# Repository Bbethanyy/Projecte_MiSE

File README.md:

View this project on [CADLAB.io](https://cadlab.io/project/27800). 

# Projecte_MiSE

**Membres del grup:** Bethany Quintero i Rossend Cera
----------------------------------------------------
## Objectiu
Dissenyar un sistema per controlar els moviments de'un Robot mitjançant un Microcontrolador MSP430.

## Elements
- Una placa base amb el Microcontrolador MSP430
- Connexió SBW o JTAG per poder programar/debugar amb una eina externa.
- Un DISPLAY LCD 
- Un Comandament format per un joystick i 1 o 2 polsadors
- El ROBOT 1(DFRobot Mcqueen plus)
- Dues LDRs
- Un mòdul UART<->Wifi

  ## Diagrama de blocs
)

## Components
| Ref. | Descripció| Datasheet |
| ------ | -----------------| ------------------|
|MSP430FR2355TPT|Microcontrolador|[Datasheet](https://www.ti.com/lit/ds/symlink/msp430fr2355.pdfts=1708776366062&ref_url=https%253A%252F%252Fwww.ti.com%252Fproduct%252FMSP430FR2355%253Fqgpn%253Dmsp430fr2355)|
|THB-1841844|Joystick| [Datasheet](https://www.mouser.es/datasheet/2/240/thb-3050713.pdf)|
|HD44780U|LCD 1602|[Datasheet](https://www.sparkfun.com/datasheets/LCD/HD44780.pdf)|
|MD21605B6W-FPTLWI3| LCD I2C| [Datasheet](https://www.farnell.com/datasheets/3164276.pdf)|
|MCCOG21605B6W-SPTLYI| LCD Text | [Datasheet](https://www.farnell.com/datasheets/2021773.pdf)|
|NSL-19M51|Detector de fotos| [Datasheet](file:///C:/Users/betha/AppData/Local/Temp/817923a0-e29a-454a-975b-60c01e8ddaef_Documents%20components%20i%20dispositius-20240224.zip.aef/LDR%20NSL-19M51.pdf)|
|...| LMV324| [Datasheet](https://www.ti.com/lit/ds/symlink/lmv324.pdf)|
|...| Trimmer tyco| [Datasheet](https://www.farnell.com/datasheets/314461.pdf)|
|...| Ultrasons HC-SR04| [Datasheet](file:///C:/Users/betha/AppData/Local/Temp/49233692-ea68-4fa0-998a-116c9ef42827_Documents%20components%20i%20dispositius-20240224.zip.827/Ultrasons%20HC-SR04%20Echo%20Locator%20Making%20it%20better.pdf)|
|...| Ultrasons HC-SR05| [Datasheet](file:///C:/Users/betha/AppData/Local/Temp/bb4ae17f-42be-418a-a625-329d45a58329_Documents%20components%20i%20dispositius-20240224.zip.329/Ultrasons%20HC-SR05_Ultrasonic_Module%20VMA306%20Schema.pdf)|
|...| Ultrasons SRF04| [Datasheet](file:///C:/Users/betha/AppData/Local/Temp/166e3fce-a4a8-462c-85ff-759b14133cc4_Documents%20components%20i%20dispositius-20240224.zip.cc4/Ultrasons%20SRF04%20Technical%20Documentation.pdf)|

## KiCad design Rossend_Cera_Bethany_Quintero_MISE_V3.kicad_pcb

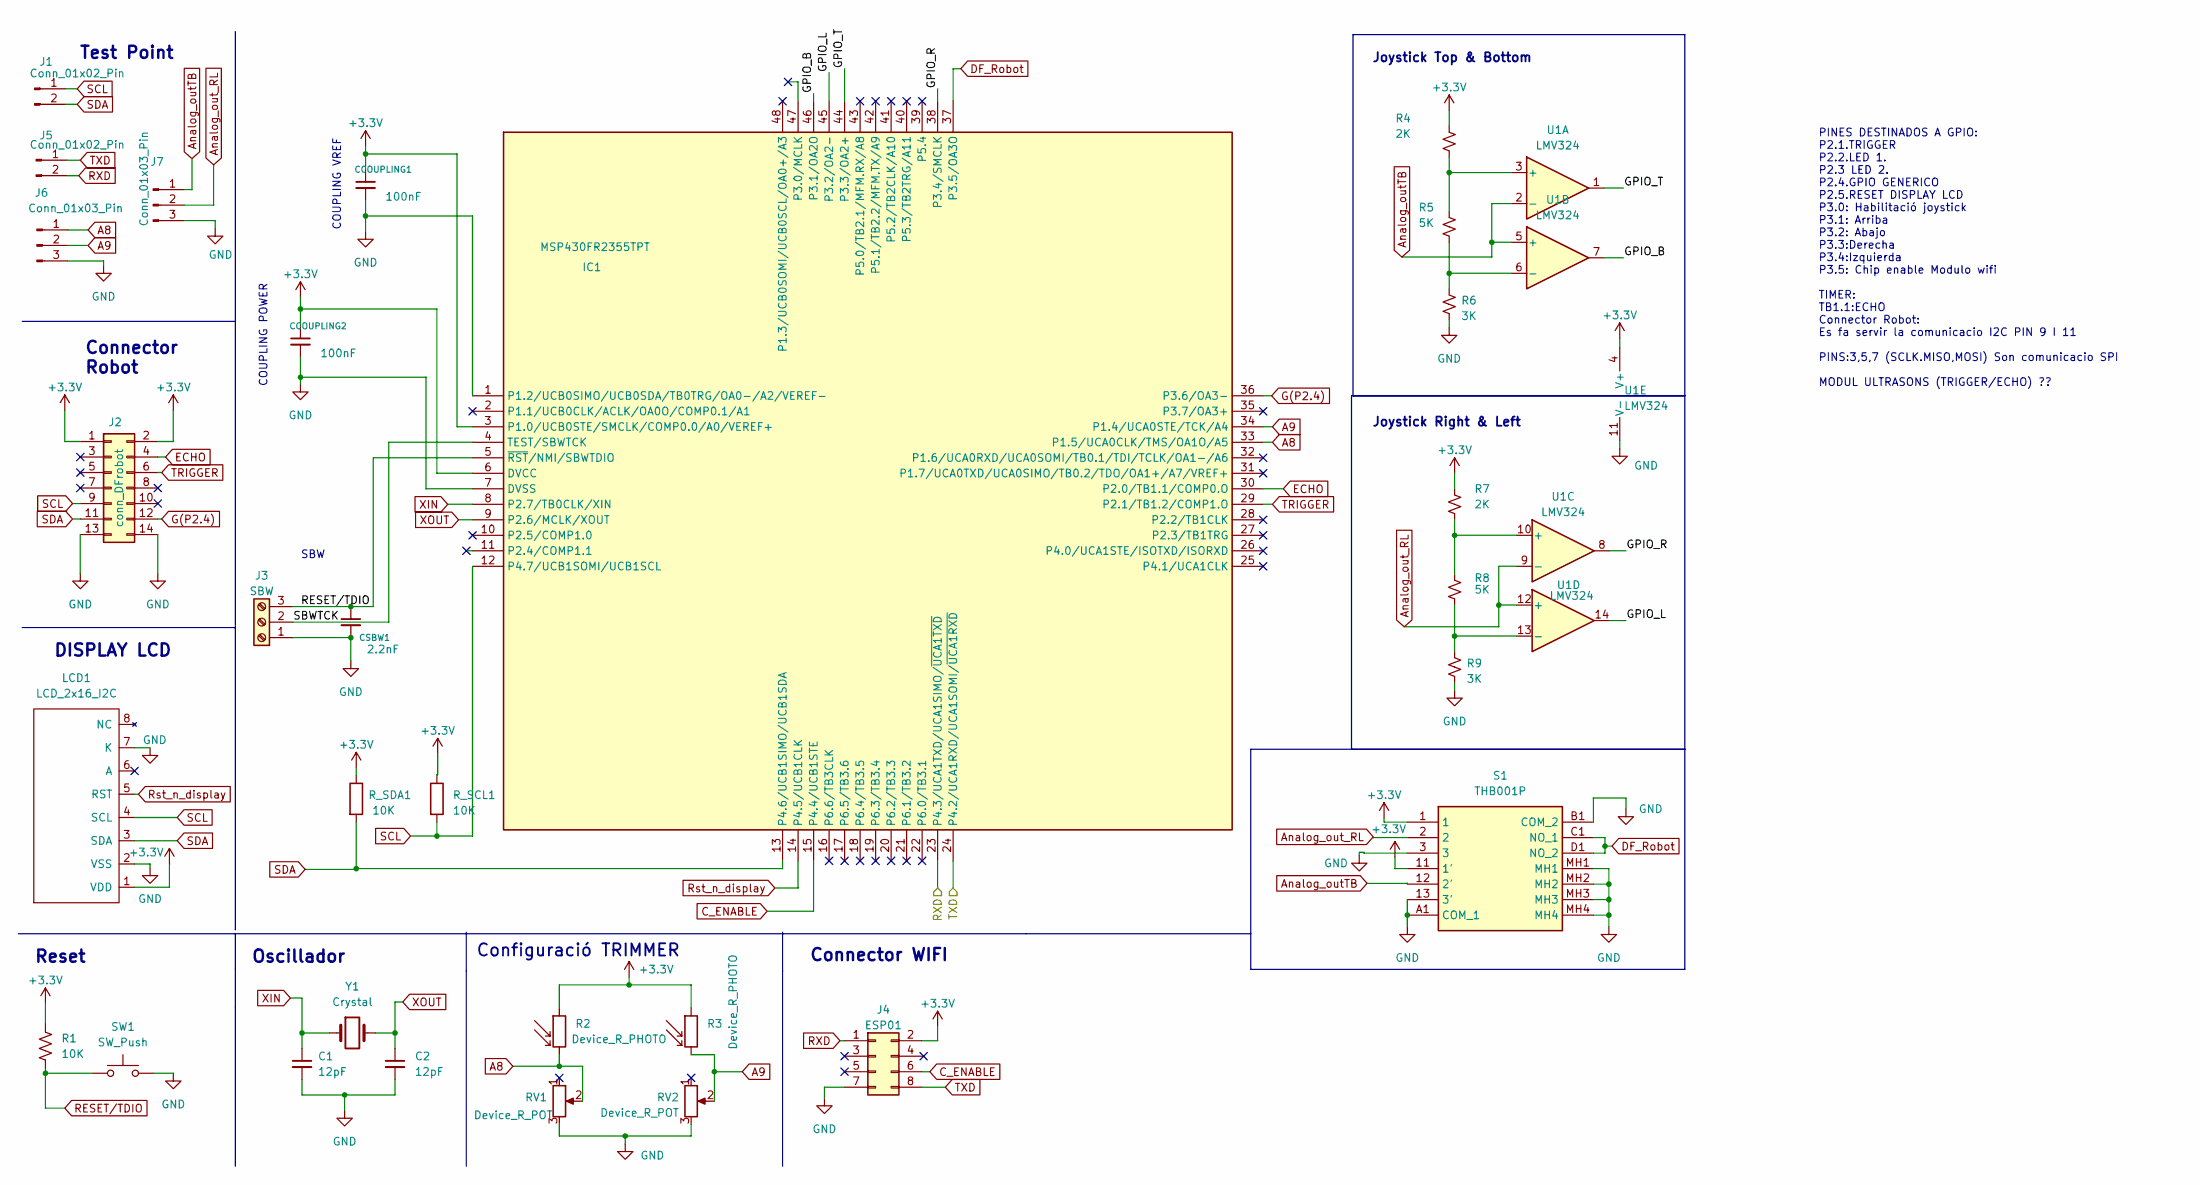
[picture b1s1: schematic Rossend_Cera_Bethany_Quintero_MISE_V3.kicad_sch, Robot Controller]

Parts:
C1, C2: 12pF; C_0805_2012Metric_Pad1.18x1.45mm_HandSolder
CCOUPLING1, CCOUPLING2: 100nF; C_0805_2012Metric_Pad1.18x1.45mm_HandSolder
CSBW1: 2.2nF; C_0805_2012Metric_Pad1.18x1.45mm_HandSolder
IC1: MSP430FR2355TPT; QFP50P900X900X160-48N; Manufacturer_Part_Number MSP430FR2355TPT; Mouser Part Number 595-MSP430FR2355TPT
J1, J5: Conn_01x02_Pin; PinHeader_1x02_P2.54mm_Vertical
J2: conn_DFrobot
J3: SBW; PinHeader_1x03_P2.54mm_Vertical
J4: ESP01; PinHeader_2x04_P2.54mm_Vertical
J6, J7: Conn_01x03_Pin; PinHeader_1x03_P2.54mm_Vertical
LCD1: LCD_2x16_I2C; LCD_2x16_I2C(Midas)
R1: 10K; R_0805_2012Metric_Pad1.20x1.40mm_HandSolder
R2, R3: Device_R_PHOTO; LDR
R4, R7: 2K; R_0805_2012Metric_Pad1.20x1.40mm_HandSolder
R5, R8: 5K; R_0805_2012Metric_Pad1.20x1.40mm_HandSolder
R6, R9: 3K; R_0805_2012Metric_Pad1.20x1.40mm_HandSolder
RV1, RV2: Device_R_POT; Trimmer_MiSE
R_SCL1: 10K; R_0805_2012Metric_Pad1.20x1.40mm_HandSolder
R_SDA1: 10K; R_0805_2012Metric_Pad1.20x1.40mm_HandSolder
S1: THB001P; Manufacturer_Part_Number THB001P; Mouser Part Number 611-THB001P
SW1: SW_Push; SW_PUSH_6mm
U1: LMV324; SOIC127P600X175-14N
Y1: Crystal; Crystal_C26-LF_D2.1mm_L6.5mm_Horizontal

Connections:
+3.3V: CCOUPLING1.1, CCOUPLING2.1, IC1.3 (P1.0/UCB0STE/SMCLK/COMP0.0/A0/VEREF+), IC1.6 (DVCC), J2.1, J2.2, J4.2, LCD1.1 (VDD), R1.1, R2.1, R3.1, R4.1, R7.1, R_SCL1.1, R_SDA1.1, S1.1, S1.11 (1'), U1.4 (V+)
/GPIO_B: IC1.46 (P3.1/OA2O), U1.7
/GPIO_L: IC1.45 (P3.2/OA2-), U1.14
/GPIO_R: IC1.38 (P3.4/SMCLK), U1.8
/GPIO_T: IC1.44 (P3.3/OA2+), U1.1
/SBWTCK: IC1.4 (TEST/SBWTCK), J3.2
A8: IC1.33 (P1.5/UCA0CLK/TMS/OA1O/A5), J6.1, R2.2, RV1.2
A9: IC1.34 (P1.4/UCA0STE/TCK/A4), J6.2, R3.2, RV2.2
Analog_outTB: J7.1, S1.12 (2'), U1.2 (-), U1.5 (+)
Analog_out_RL: J7.2, S1.2, U1.9 (-), U1.12 (+)
C_ENABLE: IC1.15 (P4.4/UCB1STE), J4.6
DF_Robot: IC1.37 (P3.5/OA3O), S1.C1 (NO_1), S1.D1 (NO_2)
ECHO: IC1.30 (P2.0/TB1.1/COMP0.O), J2.4
G(P2.4): IC1.36 (P3.6/OA3-), J2.12
GND: C1.2, C2.2, CCOUPLING1.2, CCOUPLING2.2, CSBW1.2, IC1.1 (P1.2/UCB0SIMO/UCB0SDA/TB0TRG/OA0-/A2/VE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), IC1.7 (DVSS), J2.13, J2.14, J3.1, J4.7, J6.3, J7.3, LCD1.2 (VSS), LCD1.7 (K), R6.2, R9.2, RV1.3, RV2.3, S1.3, S1.13 (3'), S1.A1 (COM_1), S1.B1 (COM_2), S1.MH1, S1.MH2, S1.MH3, S1.MH4, SW1.2, U1.11 (V-)
unnamed: R4.2, R5.1, U1.3 (+)
unnamed: R5.2, R6.1, U1.6 (-)
unnamed: R7.2, R8.1, U1.10 (+)
unnamed: R8.2, R9.1, U1.13 (-)
RESET/TDIO: CSBW1.1, IC1.5 (~RST/NMI/SBWTDIO), J3.3, R1.2, SW1.1
RXD: IC1.23 (P4.3/UCA1TXD/UCA1SIMO/~UCA1TXD), J4.1, J5.2
Rst_n_display: IC1.14 (P4.5/UCB1CLK), LCD1.5 (RST)
SCL: IC1.12 (P4.7/UCB1SOMI/UCB1SCL), J1.1, J2.9, LCD1.4 (SCL), R_SCL1.2
SDA: IC1.13 (P4.6/UCB1SIMO/UCB1SDA), J1.2, J2.11, LCD1.3 (SDA), R_SDA1.2
TRIGGER: IC1.29 (P2.1/TB1.2/COMP1.O), J2.6
TXD: IC1.24 (P4.2/UCA1RXD/UCA1SOMI/~UCA1RXD), J4.8, J5.1
XIN: C1.1, IC1.8 (P2.7/TB0CLK/XIN), Y1.1
XOUT: C2.1, IC1.9 (P2.6/MCLK/XOUT), Y1.2

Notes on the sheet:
PINES DESTINADOS A GPIO: P2.1.TRIGGER P2.2.LED 1. P2.3 LED 2. P2.4.GPIO GENERICO P2.5.RESET DISPLAY LCD P3.0: Habilitació joystick P3.1: Arriba P3.2: Abajo P3.3:Derecha P3.4:Izquierda P3.5: Chip enable Modulo wifi TIMER: TB1.1:ECHO Connector Robot: Es fa servir la comunicacio I2C PIN 9 I 11 PINS:3,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
Connector Robot
Reset
Oscillador
DISPLAY LCD
Joystick Top & Bottom
Connector WIFI
COUPLING POWER
Configuració TRIMMER
SBW
COUPLING VREF
Test Point
Joystick Right & Left

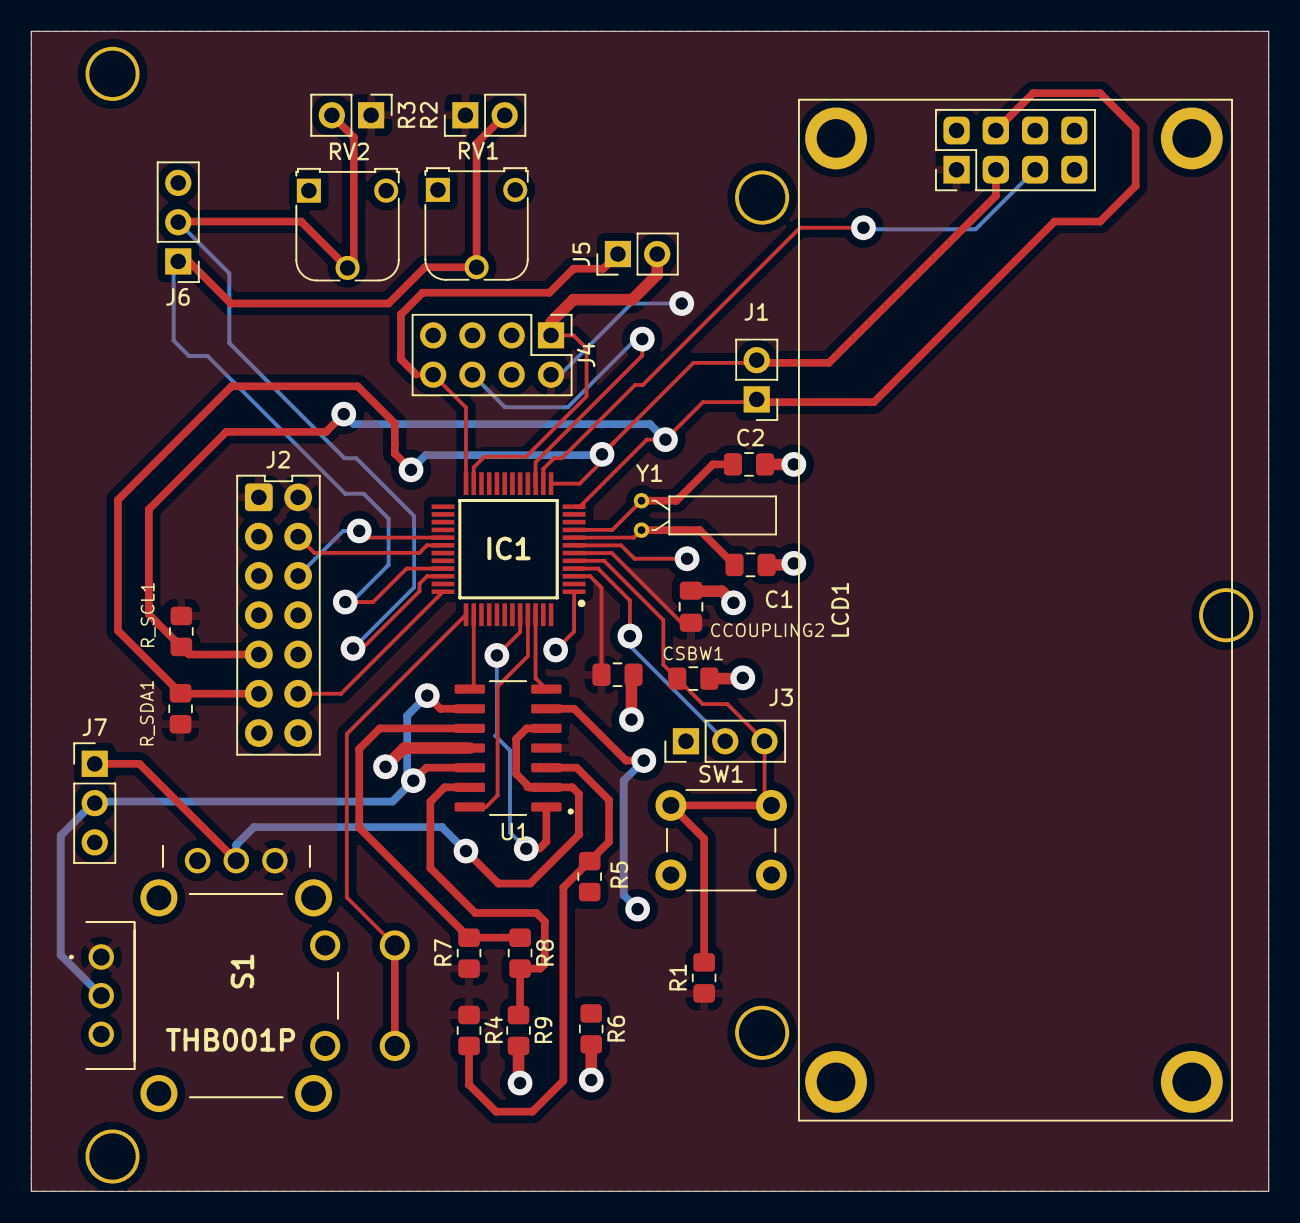
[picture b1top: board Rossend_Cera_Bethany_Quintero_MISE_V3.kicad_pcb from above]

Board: 2 copper layers, 80.0 x 75.0 mm, 31 parts (0 on the bottom side), 28 nets.

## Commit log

2024-02-24 Backlink to CADLAB.io has been added.
